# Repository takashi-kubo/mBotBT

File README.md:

# mBotBT
mBot BlueTooth Module Adapter available in Japan

Environment: KiCAD

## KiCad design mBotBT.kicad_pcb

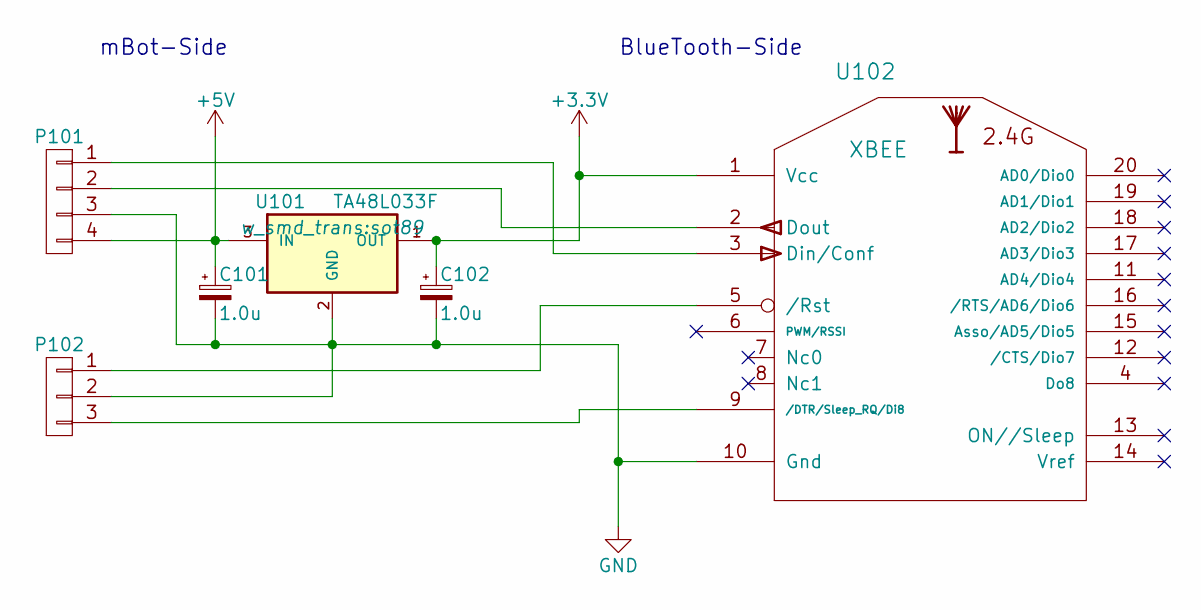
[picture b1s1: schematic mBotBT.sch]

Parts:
C101, C102: 1.0u; TantalC_SizeR_EIA-2012
P101: CONN_01X04; Pin_Header_Straight_1x04
P102: CONN_01X03; Pin_Header_Straight_1x03
U101: TA48L033F; sot89
U102: XBEE; XBee

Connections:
+3V3: C102.1, U101.1 (OUT), U102.1 (Vcc)
+5V: C101.1, P101.4, U101.3 (IN)
GND: C101.2, C102.2, P101.3, P102.2, U101.2 (GND), U102.10 (Gnd)
unnamed: P101.1, U102.3 (Din/Conf)
unnamed: P101.2, U102.2 (Dout)
unnamed: P102.1, U102.5 (/Rst)
unnamed: P102.3, U102.9 (/DTR/Sleep_RQ/Di8)

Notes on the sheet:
mBot-Side
BlueTooth-Side

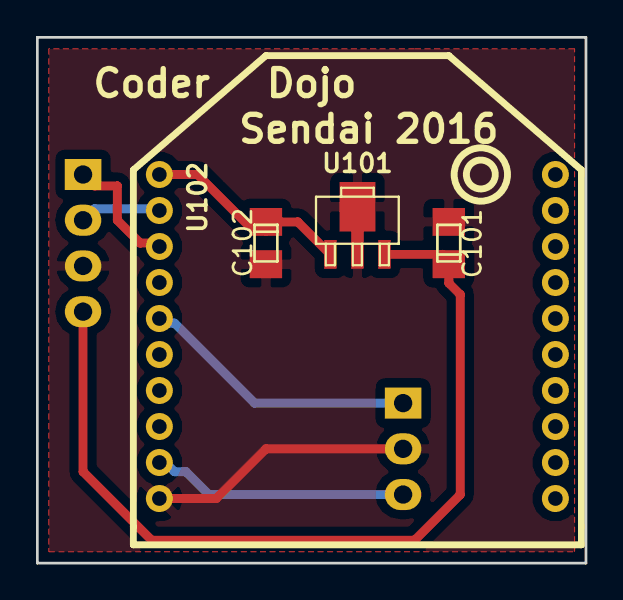
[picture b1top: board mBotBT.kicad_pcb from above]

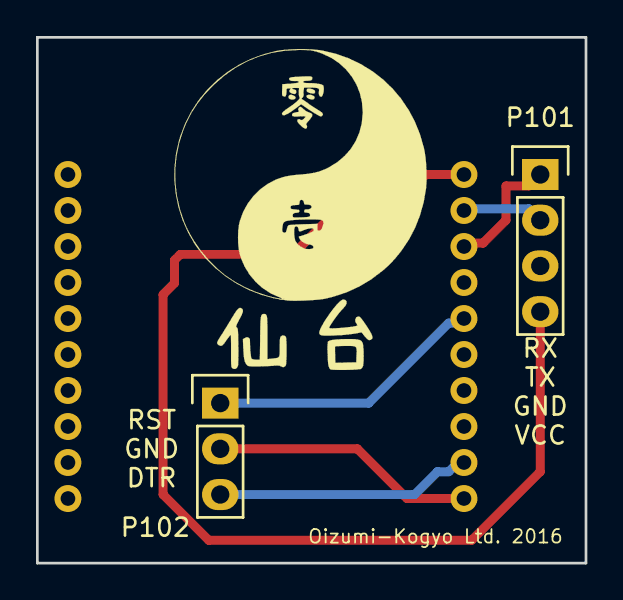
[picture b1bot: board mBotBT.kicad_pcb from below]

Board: 2 copper layers, 30.5 x 29.2 mm, 6 parts (2 on the bottom side), 7 nets.

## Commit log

2016-02-12 Import Local Files
2016-02-14 Ordring to Elecrow
2016-03-20 Bugfix
